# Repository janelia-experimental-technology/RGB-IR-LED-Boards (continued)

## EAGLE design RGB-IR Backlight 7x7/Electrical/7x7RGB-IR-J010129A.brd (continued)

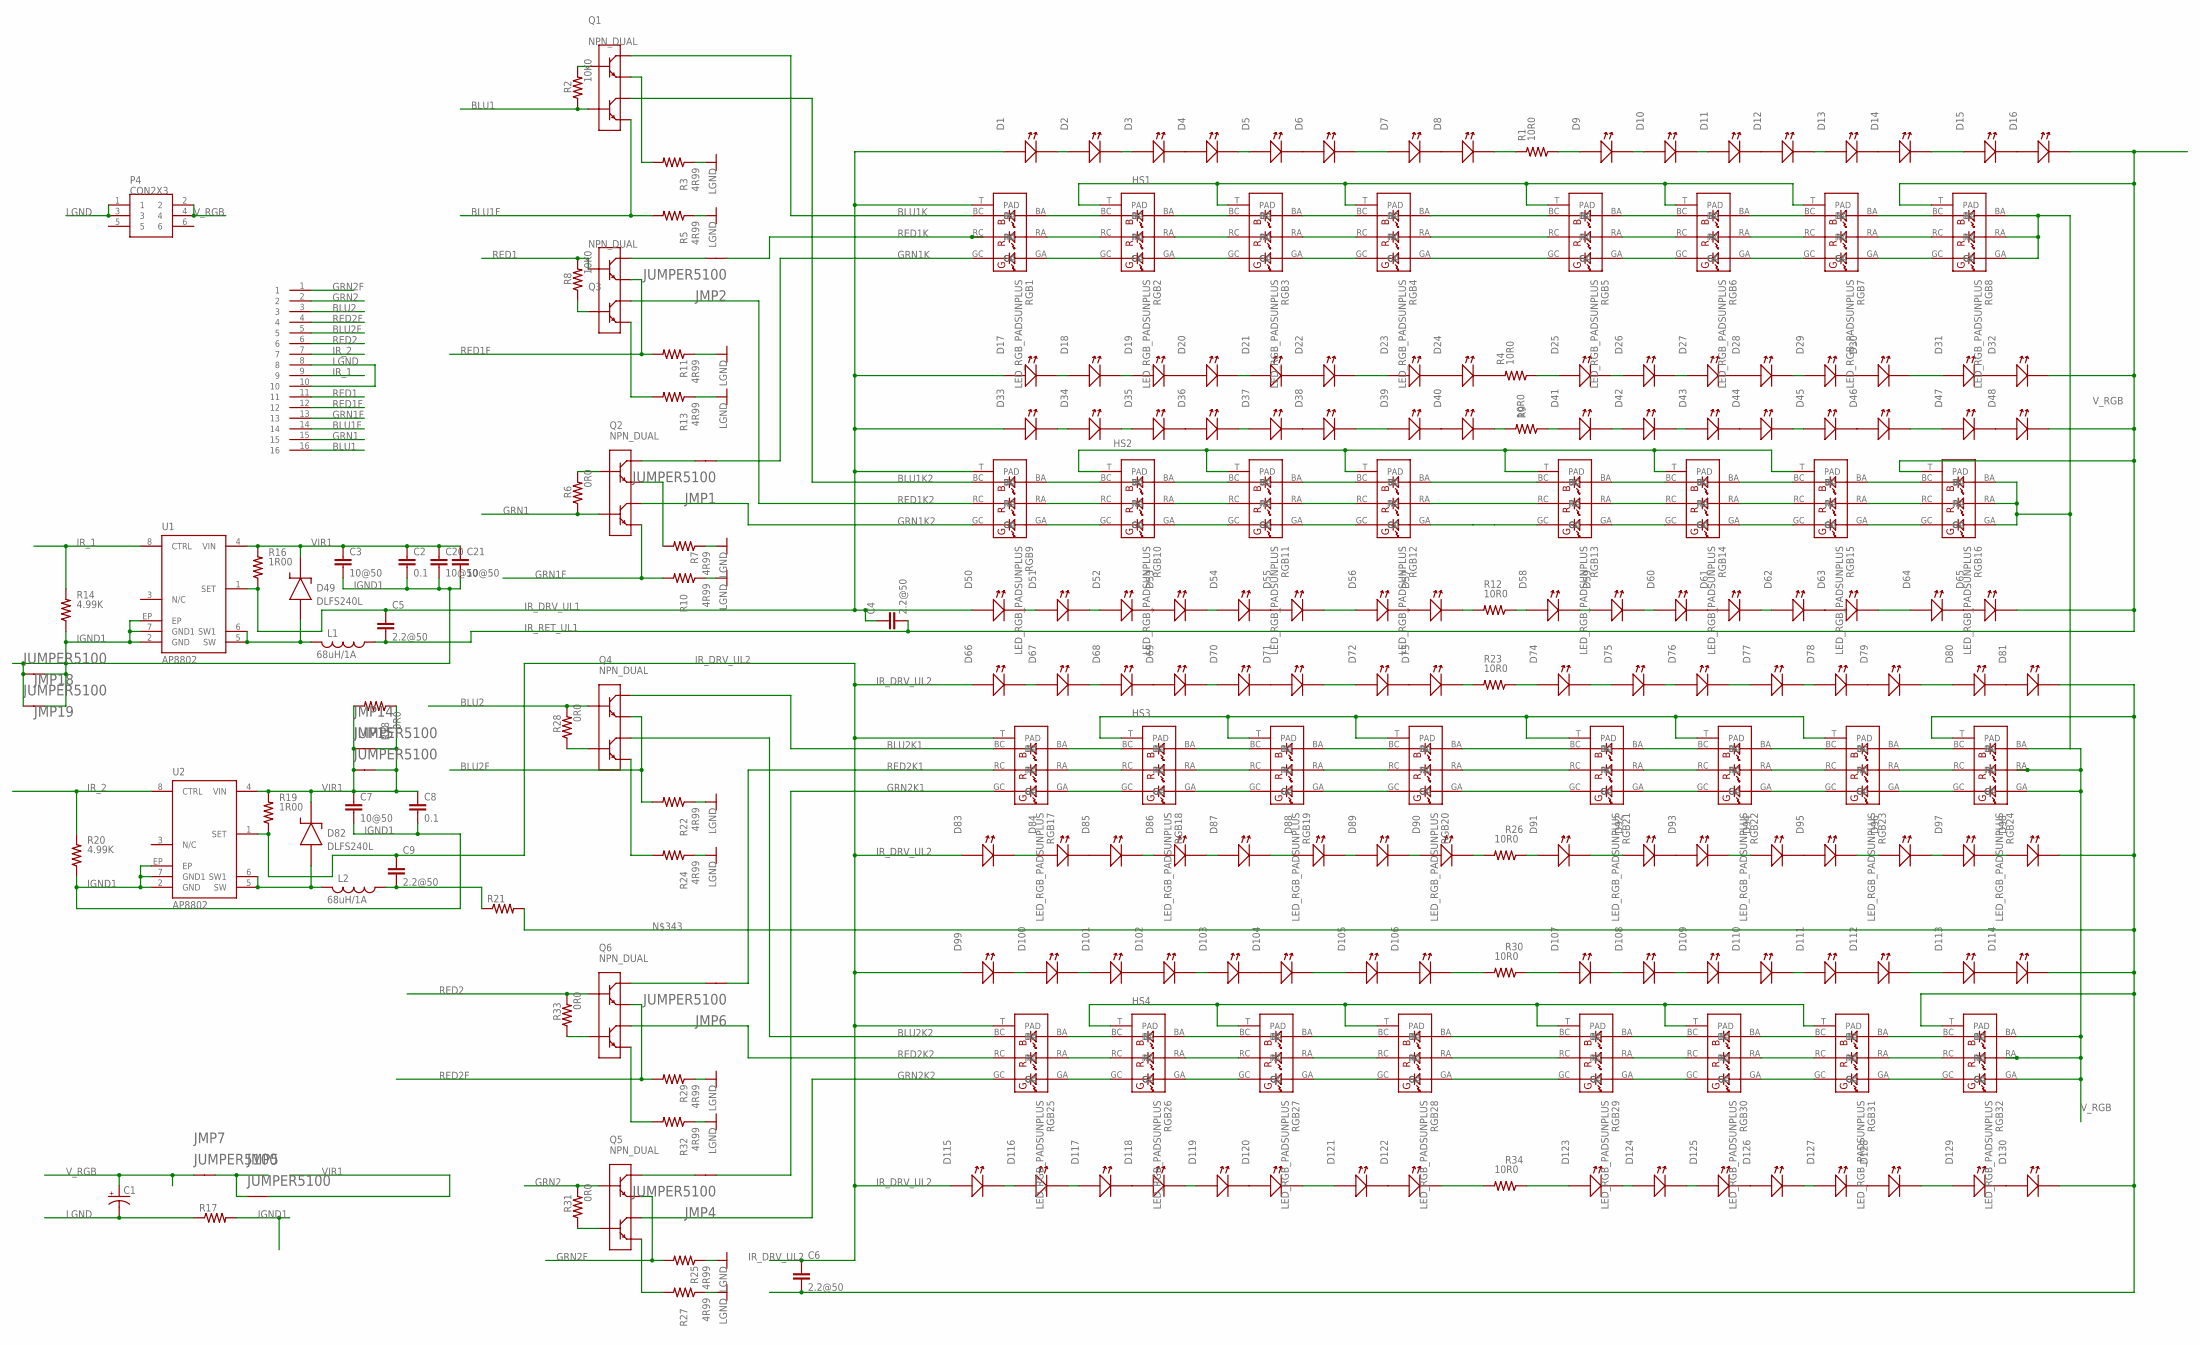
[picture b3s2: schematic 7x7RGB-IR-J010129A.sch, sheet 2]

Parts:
C1: CPOL-US153CLV-0810; 153CLV-0810
C2, C8: 0.1; 0805S
C3, C7, C20, C21: 10@50; 1210S
C4, C5, C6, C9: 2.2@50; 1206S
D1, D2, D3, D4, D5, D6, D7, D8, D9, D10, D11, D12, D13, D14, D15, D16, D17, D18, D19, D20, D21, D22, D23, D24, D25, D26, D27, D28, D29, D30, D31, D32, D33, D34, D35, D36, D37, D38, D39, D40, D41, D42, D43, D44, D45, D46, D47, D48, D50, D51, D52, D53, D54, D55, D56, D57, D58, D59, D60, D61, D62, D63, D64, D65, D66, D67, D68, D69, D70, D71, D72, D73, D74, D75, D76, D77, D78, D79, D80, D81, D83, D84, D85, D86, D87, D88, D89, D90, D91, D92, D93, D94, D95, D96, D97, D98, D99, D100, D101, D102, D103, D104, D105, D106, D107, D108, D109, D110, D111, D112, D113, D114, D115, D116, D117, D118, D119, D120, D121, D122, D123, D124, D125, D126, D127, D128, D129, D130: LEDLED_SFH4050; LED_SFH4050
D49, D82: DLFS240L; PWRDI-123
JMP1, JMP2, JMP4, JMP5, JMP6, JMP7, JMP14, JMP15, JMP18, JMP19: JUMPER5100; 5100
L1, L2: 68uH/1A; SRU8043
P1: CON162X8SM-SMALL; HEADER2X8_SM_SMALL
P4: CON2X3; 2X3_SHROUDED_SMT
Q1, Q2, Q3, Q4, Q5, Q6: NPN_DUAL; LFPAK56D
R1, R4, R9, R12, R23, R26, R30, R34: 10R0; 1206S
R2, R8: 10K0; 1206S
R3, R5, R7, R10, R11, R13, R22, R24, R25, R27, R29, R32: 4R99; R2512
R6, R28, R31, R33: 0R0; 1206S
R14, R20: 4.99K; 0805S
R16, R19: 1R00; 1206S
R17, R21: RESISTOR_SM1206S; 1206S
R18: 0R0; R1206
RGB1, RGB2, RGB3, RGB4, RGB5, RGB6, RGB7, RGB8, RGB9, RGB10, RGB11, RGB12, RGB13, RGB14, RGB15, RGB16, RGB17, RGB18, RGB19, RGB20, RGB21, RGB22, RGB23, RGB24, RGB25, RGB26, RGB27, RGB28, RGB29, RGB30, RGB31, RGB32: LED_RGB_PADSUNPLUS; SUNPLUS_RGB
U1, U2: AP8802; SOIC8-EP

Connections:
BLU1: P1.16, Q1.4 (B2), R2.1
BLU1F: P1.14, Q1.3 (E2), R5.2
BLU1K: Q1.7 (C1), Q1.8 (C1), Q1.78 (C1), RGB1.BC
BLU1K2: Q1.5 (C2), Q1.6 (C2), Q1.56 (C2), RGB9.BC
BLU2: P1.3, Q4.2 (B1), R28.2
BLU2F: P1.5, Q4.1 (E1), R22.2
BLU2K1: Q4.7 (C1), Q4.8 (C1), Q4.78 (C1), RGB17.BC
BLU2K2: Q4.5 (C2), Q4.6 (C2), Q4.56 (C2), RGB25.BC
G1: Q5.3 (E2), R27.2
G4A1: Q5.4 (B2), R31.1
GRN1: P1.15, Q2.4 (B2), R6.1
GRN1F: P1.13, Q2.3 (E2), R10.2
GRN1K: JMP1.1, RGB1.GC
GRN1K2: Q2.5 (C2), Q2.6 (C2), Q2.56 (C2), RGB9.GC
GRN2: P1.2, Q5.2 (B1), R31.2
GRN2F: P1.1, Q5.1 (E1), R25.2
GRN2K1: JMP4.1, RGB17.GC
GRN2K2: Q5.5 (C2), Q5.6 (C2), Q5.56 (C2), RGB25.GC
HS1: RGB2.T (PAD), RGB3.T (PAD), RGB4.T (PAD), RGB5.T (PAD), RGB6.T (PAD), RGB7.T (PAD)
HS2: RGB10.T (PAD), RGB11.T (PAD), RGB12.T (PAD), RGB13.T (PAD), RGB14.T (PAD), RGB15.T (PAD)
HS3: RGB18.T (PAD), RGB19.T (PAD), RGB20.T (PAD), RGB21.T (PAD), RGB22.T (PAD), RGB23.T (PAD)
HS4: RGB26.T (PAD), RGB27.T (PAD), RGB28.T (PAD), RGB29.T (PAD), RGB30.T (PAD), RGB31.T (PAD)
IGND1: C2.2, C3.2, C7.2, C8.2, C20.2, C21.2, JMP18.1, JMP18.2, JMP19.1, JMP19.2, R14.1, R17.2, R20.1, U1.2 (GND), U1.7 (GND1), U1.EP, U2.2 (GND), U2.7 (GND1), U2.EP
IR_1: P1.9, R14.2, U1.8 (CTRL)
IR_2: P1.7, R20.2, U2.8 (CTRL)
IR_DRV_UL1: C4.1, C5.1, D1.A, D17.A, D33.A, D50.A, R16.1, RGB1.T (PAD), RGB9.T (PAD), U1.1 (SET)
IR_DRV_UL2: C6.1, C9.1, D66.A, D83.A, D99.A, D115.A, R19.1, RGB17.T (PAD), RGB25.T (PAD), U2.1 (SET)
IR_RET_UL1: C4.2, C5.2, D16.C (K), D32.C (K), D48.C (K), D65.C (K), L1.1, RGB8.T (PAD), RGB16.T (PAD)
LGND: C1.-, P1.8, P1.10, P4.1, P4.3, R3.1, R5.1, R7.1, R10.1, R11.1, R13.1, R17.1, R22.1, R24.1, R25.1, R27.1, R29.1, R32.1; also elsewhere on the board
unnamed: RGB15.GA, RGB16.GC
unnamed: RGB14.GA, RGB15.GC
unnamed: RGB13.GA, RGB14.GC
unnamed: RGB12.GA, RGB13.GC
unnamed: RGB11.GA, RGB12.GC
unnamed: RGB10.GA, RGB11.GC
unnamed: RGB9.GA, RGB10.GC
unnamed: RGB15.RA, RGB16.RC
unnamed: RGB14.RA, RGB15.RC
unnamed: RGB13.RA, RGB14.RC
unnamed: RGB12.RA, RGB13.RC
unnamed: RGB11.RA, RGB12.RC
unnamed: RGB10.RA, RGB11.RC
unnamed: RGB9.RA, RGB10.RC
unnamed: RGB9.BA, RGB10.BC
unnamed: RGB10.BA, RGB11.BC
unnamed: RGB11.BA, RGB12.BC
unnamed: RGB12.BA, RGB13.BC
unnamed: RGB13.BA, RGB14.BC
unnamed: RGB14.BA, RGB15.BC
unnamed: RGB15.BA, RGB16.BC
unnamed: D51.C (K), D52.A
unnamed: D52.C (K), D53.A
unnamed: D54.C (K), D55.A
unnamed: D56.C (K), D57.A
unnamed: D50.C (K), D51.A
unnamed: D53.C (K), D54.A
unnamed: D55.C (K), D56.A
unnamed: D59.C (K), D60.A
unnamed: D60.C (K), D61.A
unnamed: D62.C (K), D63.A
unnamed: D64.C (K), D65.A
unnamed: D58.C (K), D59.A
unnamed: D61.C (K), D62.A
unnamed: D63.C (K), D64.A
unnamed: D34.C (K), D35.A
unnamed: D35.C (K), D36.A
unnamed: D37.C (K), D38.A
unnamed: D39.C (K), D40.A
unnamed: D33.C (K), D34.A
unnamed: D36.C (K), D37.A
unnamed: D38.C (K), D39.A
unnamed: D42.C (K), D43.A
unnamed: D43.C (K), D44.A
unnamed: D45.C (K), D46.A
unnamed: D47.C (K), D48.A
unnamed: D41.C (K), D42.A
unnamed: D44.C (K), D45.A
unnamed: D46.C (K), D47.A
unnamed: RGB23.GA, RGB24.GC
unnamed: RGB22.GA, RGB23.GC
unnamed: RGB21.GA, RGB22.GC
unnamed: RGB20.GA, RGB21.GC
unnamed: RGB19.GA, RGB20.GC
unnamed: RGB18.GA, RGB19.GC
unnamed: RGB17.GA, RGB18.GC
unnamed: RGB23.RA, RGB24.RC
unnamed: RGB22.RA, RGB23.RC
unnamed: RGB21.RA, RGB22.RC
unnamed: RGB20.RA, RGB21.RC
unnamed: RGB19.RA, RGB20.RC
unnamed: RGB18.RA, RGB19.RC
unnamed: RGB17.RA, RGB18.RC
unnamed: RGB17.BA, RGB18.BC
unnamed: RGB18.BA, RGB19.BC
unnamed: RGB19.BA, RGB20.BC
unnamed: RGB20.BA, RGB21.BC
unnamed: RGB21.BA, RGB22.BC
unnamed: RGB22.BA, RGB23.BC
unnamed: RGB23.BA, RGB24.BC
unnamed: D67.C (K), D68.A
unnamed: D68.C (K), D69.A
unnamed: D70.C (K), D71.A
unnamed: D72.C (K), D73.A
unnamed: D66.C (K), D67.A
unnamed: D69.C (K), D70.A
unnamed: D71.C (K), D72.A
unnamed: D75.C (K), D76.A
unnamed: D76.C (K), D77.A
unnamed: D78.C (K), D79.A
unnamed: D80.C (K), D81.A
unnamed: D74.C (K), D75.A
unnamed: D77.C (K), D78.A
unnamed: D79.C (K), D80.A
unnamed: D84.C (K), D85.A
unnamed: D85.C (K), D86.A
unnamed: D87.C (K), D88.A
unnamed: D89.C (K), D90.A
unnamed: D83.C (K), D84.A
unnamed: D86.C (K), D87.A
unnamed: D88.C (K), D89.A
unnamed: D92.C (K), D93.A
unnamed: D94.C (K), D95.A
unnamed: D96.C (K), D97.A
unnamed: D91.C (K), D92.A
unnamed: D93.C (K), D94.A
unnamed: D95.C (K), D96.A
unnamed: RGB7.GA, RGB8.GC
unnamed: RGB6.GA, RGB7.GC
unnamed: RGB5.GA, RGB6.GC
unnamed: RGB4.GA, RGB5.GC
unnamed: RGB3.GA, RGB4.GC
unnamed: RGB2.GA, RGB3.GC
unnamed: RGB1.GA, RGB2.GC
unnamed: RGB7.RA, RGB8.RC
unnamed: RGB6.RA, RGB7.RC
unnamed: RGB5.RA, RGB6.RC
unnamed: RGB4.RA, RGB5.RC
unnamed: RGB3.RA, RGB4.RC
unnamed: RGB2.RA, RGB3.RC
unnamed: RGB1.RA, RGB2.RC
unnamed: RGB1.BA, RGB2.BC
unnamed: RGB2.BA, RGB3.BC
unnamed: RGB3.BA, RGB4.BC
unnamed: RGB4.BA, RGB5.BC
unnamed: RGB5.BA, RGB6.BC
unnamed: RGB6.BA, RGB7.BC
unnamed: RGB7.BA, RGB8.BC
unnamed: D2.C (K), D3.A
unnamed: D3.C (K), D4.A
unnamed: D5.C (K), D6.A
unnamed: D7.C (K), D8.A
unnamed: D1.C (K), D2.A
unnamed: D4.C (K), D5.A
unnamed: D6.C (K), D7.A
unnamed: D10.C (K), D11.A
unnamed: D11.C (K), D12.A
unnamed: D13.C (K), D14.A
unnamed: D15.C (K), D16.A
unnamed: D9.C (K), D10.A
unnamed: D12.C (K), D13.A
unnamed: D14.C (K), D15.A
unnamed: D18.C (K), D19.A
unnamed: D19.C (K), D20.A
unnamed: D21.C (K), D22.A
unnamed: D23.C (K), D24.A
unnamed: D17.C (K), D18.A
unnamed: D20.C (K), D21.A
unnamed: D22.C (K), D23.A
unnamed: D26.C (K), D27.A
unnamed: D27.C (K), D28.A
unnamed: D29.C (K), D30.A
unnamed: D31.C (K), D32.A
unnamed: D25.C (K), D26.A
unnamed: D28.C (K), D29.A
unnamed: D30.C (K), D31.A
unnamed: Q1.1 (E1), R3.2
unnamed: RGB31.GA, RGB32.GC
unnamed: RGB30.GA, RGB31.GC
unnamed: RGB29.GA, RGB30.GC
unnamed: RGB28.GA, RGB29.GC
unnamed: RGB27.GA, RGB28.GC
unnamed: RGB26.GA, RGB27.GC
unnamed: RGB25.GA, RGB26.GC
unnamed: RGB31.RA, RGB32.RC
unnamed: RGB30.RA, RGB31.RC
unnamed: RGB29.RA, RGB30.RC
unnamed: RGB28.RA, RGB29.RC
unnamed: RGB27.RA, RGB28.RC
unnamed: RGB26.RA, RGB27.RC
unnamed: RGB25.RA, RGB26.RC
unnamed: RGB25.BA, RGB26.BC
unnamed: RGB26.BA, RGB27.BC
unnamed: RGB27.BA, RGB28.BC
unnamed: RGB28.BA, RGB29.BC
unnamed: RGB29.BA, RGB30.BC
unnamed: RGB30.BA, RGB31.BC
unnamed: RGB31.BA, RGB32.BC
unnamed: D100.C (K), D101.A
unnamed: D101.C (K), D102.A
unnamed: D103.C (K), D104.A
unnamed: D105.C (K), D106.A
unnamed: D99.C (K), D100.A
unnamed: D102.C (K), D103.A
unnamed: D104.C (K), D105.A
unnamed: D108.C (K), D109.A
unnamed: D109.C (K), D110.A
unnamed: D111.C (K), D112.A
unnamed: D113.C (K), D114.A
unnamed: D107.C (K), D108.A
unnamed: D110.C (K), D111.A
unnamed: D112.C (K), D113.A
unnamed: D116.C (K), D117.A
unnamed: D117.C (K), D118.A
unnamed: D119.C (K), D120.A
unnamed: D121.C (K), D122.A
unnamed: D115.C (K), D116.A
unnamed: D118.C (K), D119.A
unnamed: D120.C (K), D121.A
unnamed: D124.C (K), D125.A
unnamed: D125.C (K), D126.A
unnamed: D127.C (K), D128.A
unnamed: D129.C (K), D130.A
unnamed: D123.C (K), D124.A
unnamed: D126.C (K), D127.A
unnamed: D128.C (K), D129.A
unnamed: JMP2.2, Q3.7 (C1), Q3.8 (C1), Q3.78 (C1)
unnamed: JMP1.2, Q2.7 (C1), Q2.8 (C1), Q2.78 (C1)
unnamed: Q1.2 (B1), R2.2
unnamed: D97.C (K), D98.A
unnamed: JMP6.2, Q6.7 (C1), Q6.8 (C1), Q6.78 (C1)
unnamed: JMP4.2, Q5.7 (C1), Q5.8 (C1), Q5.78 (C1)
unnamed: D49.A, L1.2, U1.5 (SW), U1.6 (SW1)
unnamed: D82.A, L2.2, U2.5 (SW), U2.6 (SW1)
unnamed: C6.2, D81.C (K), D98.C (K), D114.C (K), D130.C (K), R21.2, RGB24.T (PAD), RGB32.T (PAD)
unnamed: C9.2, L2.1, R21.1
unnamed: JMP5.1, JMP7.2
unnamed: Q6.4 (B2), R33.1
unnamed: Q4.4 (B2), R28.1
unnamed: Q4.3 (E2), R24.2
unnamed: Q3.3 (E2), R13.2
unnamed: Q3.4 (B2), R8.1
unnamed: Q2.1 (E1), R7.2
unnamed: Q2.2 (B1), R6.2
unnamed: D9.A, R1.1
unnamed: D8.C (K), R1.2
unnamed: D24.C (K), R4.2
unnamed: D25.A, R4.1
unnamed: D41.A, R9.1
unnamed: D40.C (K), R9.2
unnamed: D58.A, R12.1
unnamed: D57.C (K), R12.2
unnamed: D73.C (K), R23.2
unnamed: D74.A, R23.1
unnamed: D91.A, R26.1
unnamed: D90.C (K), R26.2
unnamed: D107.A, R30.1
unnamed: D106.C (K), R30.2
unnamed: D123.A, R34.1
unnamed: D122.C (K), R34.2
R1: Q6.3 (E2), R32.2
RED1: P1.11, Q3.2 (B1), R8.2
RED1F: P1.12, Q3.1 (E1), R11.2
RED1K: JMP2.1, RGB1.RC
RED1K2: Q3.5 (C2), Q3.6 (C2), Q3.56 (C2), RGB9.RC
RED2: P1.6, Q6.2 (B1), R33.2
RED2F: P1.4, Q6.1 (E1), R29.2
RED2K1: JMP6.1, RGB17.RC
RED2K2: Q6.5 (C2), Q6.6 (C2), Q6.56 (C2), RGB25.RC
VIR1: C2.1, C3.1, C7.1, C8.1, C20.1, C21.1, D49.K, D82.K, JMP5.2, JMP14.1, JMP14.2, JMP15.1, JMP15.2, R16.2, R18.1, R18.2, R19.2, U1.4 (VIN), U2.4 (VIN)
V_RGB: C1.+, JMP7.1, P4.2, P4.4, RGB8.BA, RGB8.GA, RGB8.RA, RGB16.BA, RGB16.GA, RGB16.RA, RGB24.BA, RGB24.GA, RGB24.RA, RGB32.BA, RGB32.GA, RGB32.RA; also elsewhere on the board

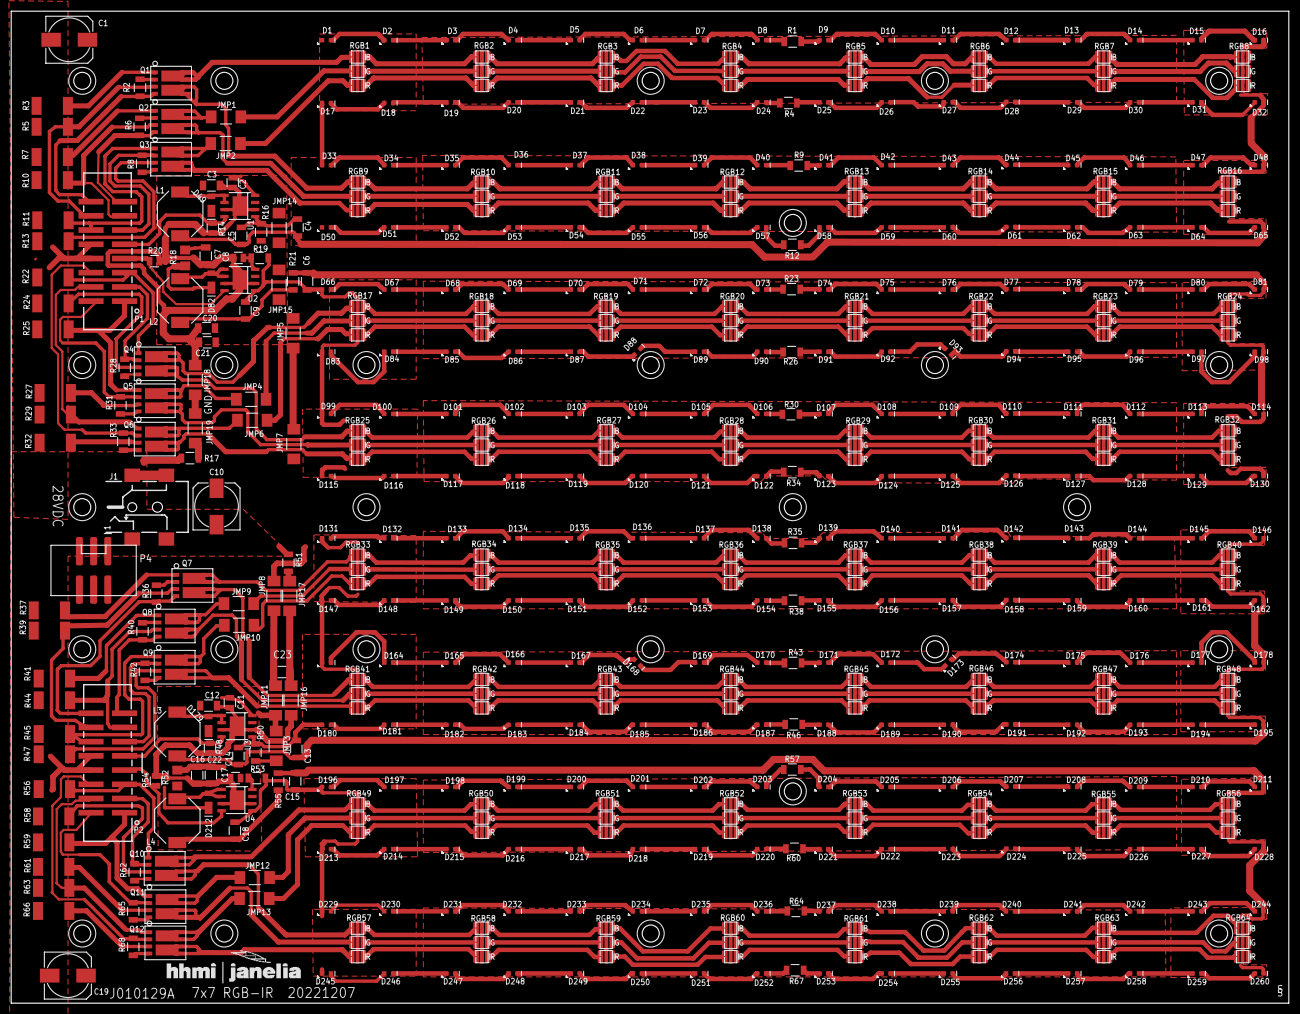
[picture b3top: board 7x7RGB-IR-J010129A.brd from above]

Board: 2 copper layers, 228.3 x 177.3 mm, 485 parts (0 on the bottom side), 537 nets.

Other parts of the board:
S1, S2, S3, S4, S5, S6, S7, S8, S9, S10, S11, S12, S13, S14, S15, S16, S17, S18, S19, S20, S21, S22, S23, S24, S25, S26, S27, S28: SCREW; 4-40SOCKET

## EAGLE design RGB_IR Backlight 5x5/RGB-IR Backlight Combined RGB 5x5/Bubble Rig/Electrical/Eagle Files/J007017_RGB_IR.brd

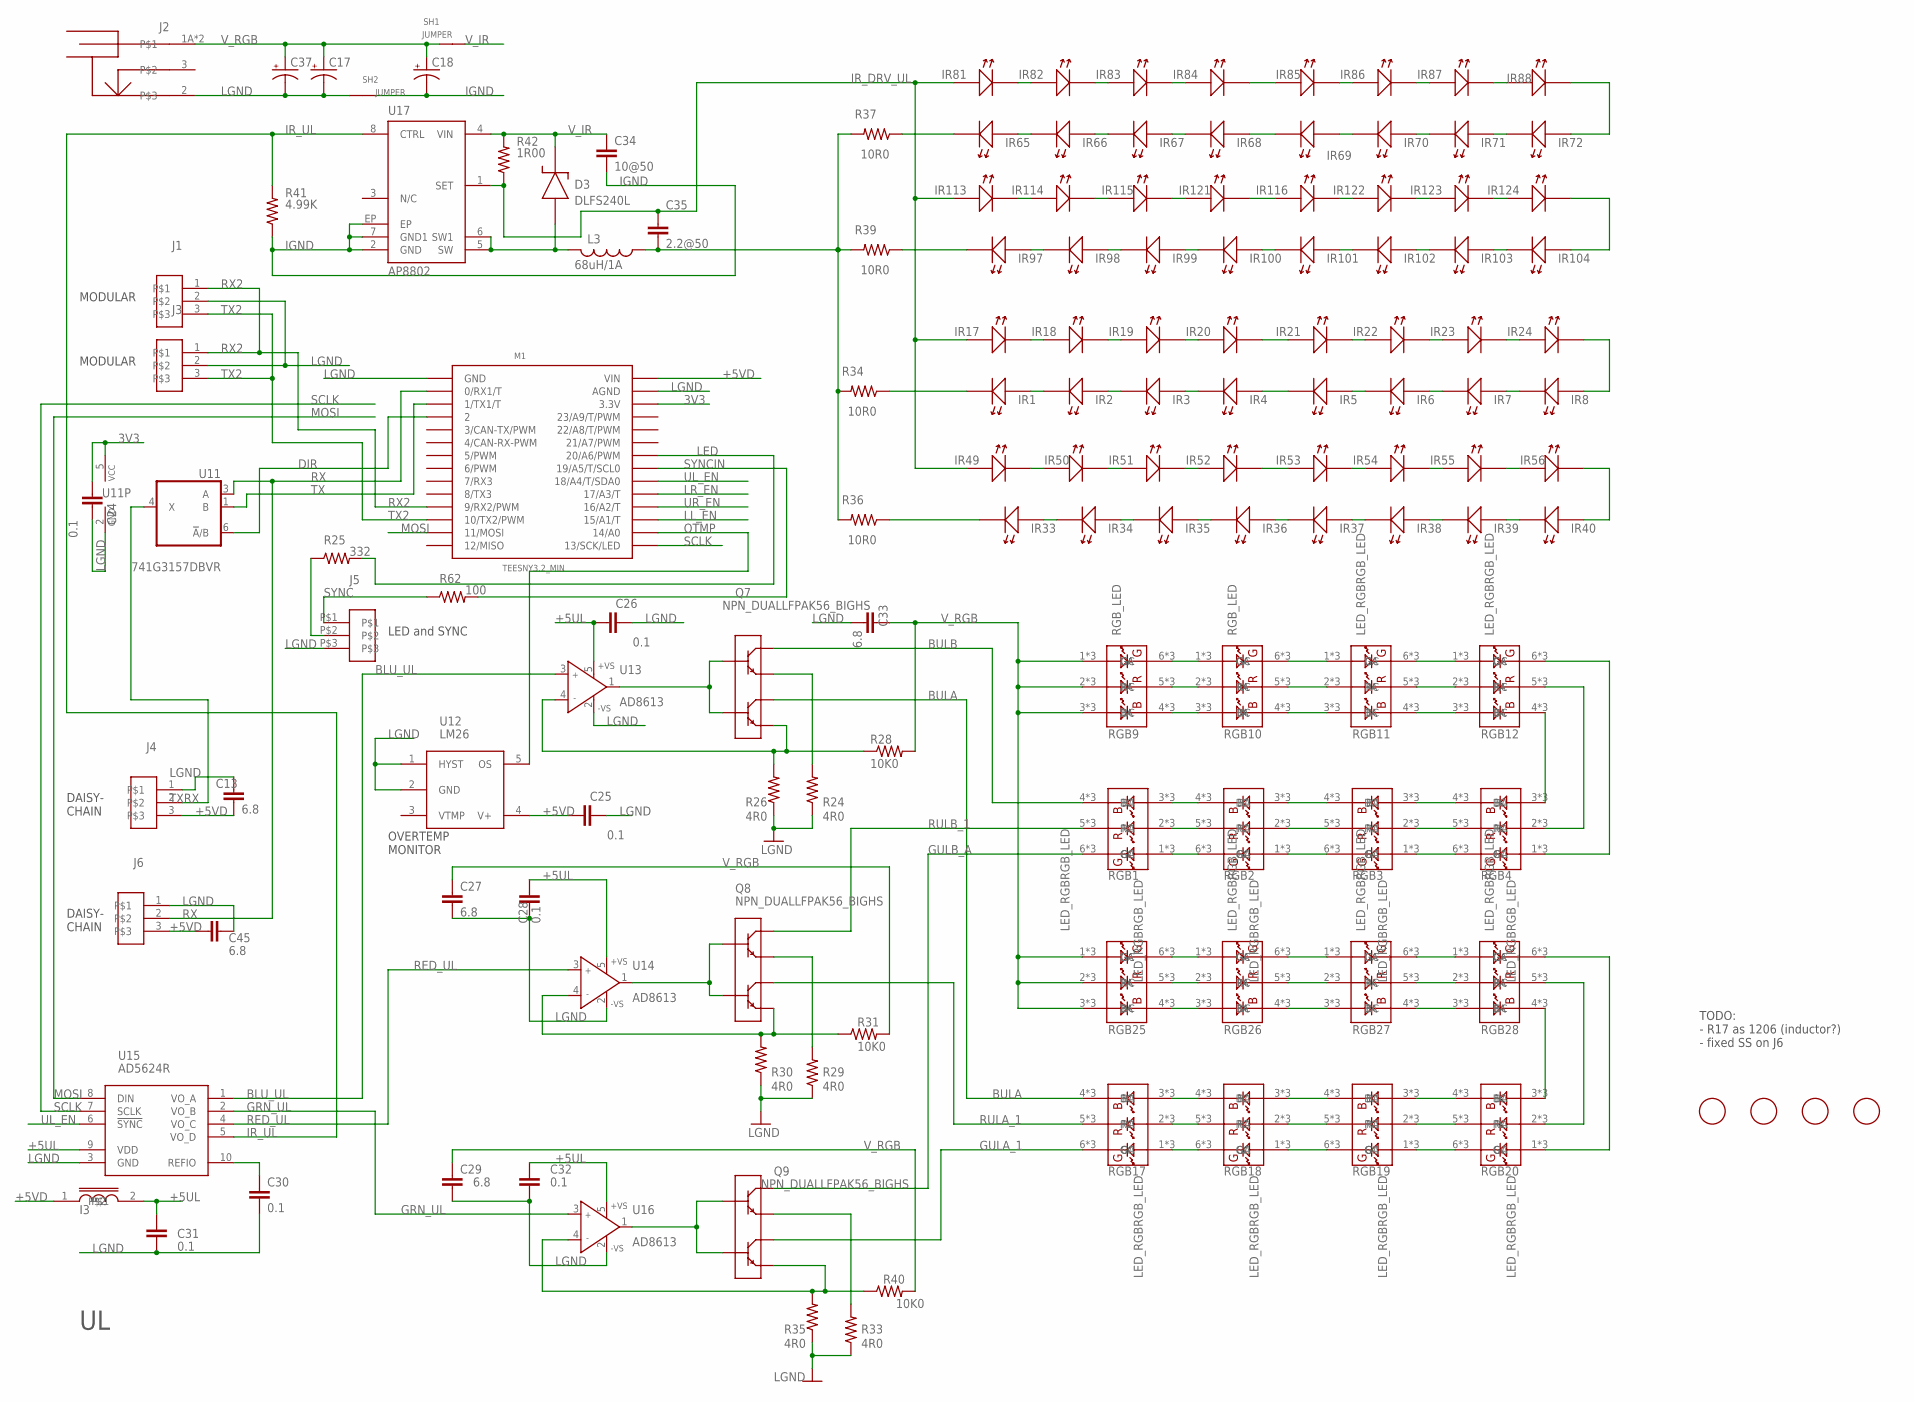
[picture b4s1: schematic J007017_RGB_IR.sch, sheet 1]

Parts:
$$U$1, $$U$2, $$U$3: FIDUCIAL; FIDUCIAL_1MM
C13, C27, C29, C33, C45: 6.8; 1210S
C17, C18, C37: CPOL-US153CLV-0810; 153CLV-0810
C24, C25, C26, C28, C30, C31, C32: 0.1; 0603S
C34: 10@50; 1210S
C35: 2.2@50; 1206S
D3: DLFS240L; PWRDI-123
I3: INDUCTOR0805S; 0805S
IR1: LEDLED_SFH4050_A; LED_SFH4045_HEAT_A
IR2, IR3, IR4, IR5, IR6, IR7, IR8, IR17, IR18, IR19, IR20, IR21, IR22, IR23, IR24, IR33, IR34, IR35, IR36, IR37, IR38, IR39, IR40, IR49, IR50, IR51, IR52, IR53, IR54, IR55, IR56, IR65, IR66, IR67, IR68, IR69, IR70, IR71, IR72, IR81, IR82, IR83, IR84, IR85, IR86, IR87, IR88, IR97, IR98, IR99, IR100, IR101, IR102, IR103, IR104, IR113, IR114, IR115, IR116, IR121, IR122, IR123: LEDLED_SFH4050_HEAT; LED_SFH4050_HEAT
IR124: LEDLED_SFH4050; LED_SFH4050
J1: CON3AMP-3-SM-RA-X; AMP-3-SM-RA-X
J2: POWER_JACK_SHUNTPJ-002; PJ-002
J3: CON3AMP_3_SM; AMP_3_SM
J4, J6: CON3TE-3-SM-V; TE_3_SM-V
J5: CON3DF13-3-V-SM; DF13_3_V_SM
L3: 68uH/1A; SRU8043
M1: TEESNY3.2_MIN; TEENSY3.2_MIN_SM
Q7, Q8, Q9: NPN_DUALLFPAK56_BIGHS; LFPAK56_HS2
R24, R26, R29, R30, R33, R35: 4R0; 1812
R25: 332; 0805S
R28, R31, R40: 10K0; 1206S
R34, R36, R37, R39: 10R0; 1206S
R41: 4.99K; 0805S
R42: 1R00; 1206S
R62: 100; 0805S
RGB1, RGB2, RGB3, RGB4, RGB11, RGB12, RGB17, RGB18, RGB19, RGB20, RGB25, RGB26, RGB27, RGB28: LED_RGBRGB_LED; OVSPRGB_HS_FIXED
RGB9, RGB10: RGB_LED; OVSPRGB_HS_FIXED
SH1, SH2: JUMPER
U11: 741G3157DBVR; DBV_R-PDSO-G6
U12: LM26; SOT23-5
U13, U14, U16: AD8613; SOT23-5
U15: AD5624R; MSOP10
U17: AP8802; SOIC8-EP
U$2: FIDUCIAL; FIDUCIAL_1MM

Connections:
3V3: C24.1, M1.26 (3.3V), U11.5 (VCC)
+5UL: C26.1, C28.1, C31.1, C32.1, I3.2, U13.5 (+VS), U14.5 (+VS), U15.9 (VDD), U16.5 (+VS)
+5VD: C13.2, C25.1, C45.1, I3.1, J4.3, J6.3, M1.28 (VIN), U12.4 (V+); also elsewhere on the board
BLU_UL: U13.3 (IN+), U15.1 (VO_A)
BULA: Q7.5 (C2), Q7.5A (C2), Q7.5A1 (C2), Q7.5B (C2), Q7.5C (C2), Q7.5C1 (C2), Q7.5C2 (C2), Q7.6 (C2), Q7.56 (C2), Q7.56A (C2), Q7.56B (C2), RGB17.4 (BC), RGB17.4A (BC), RGB17.4B (BC)
BULB: Q7.7 (C1), Q7.8 (C1), Q7.8A (C1), Q7.8B (C1), Q7.8C (C1), Q7.8C1 (C1), Q7.8C2 (C1), Q7.8C3 (C1), Q7.78 (C1), Q7.78A (C1), Q7.78B (C1), RGB1.4 (BC), RGB1.4A (BC), RGB1.4B (BC)
DIR: M1.4 (2), U11.6 (!A!/B)
GRN_UL: U15.2 (VO_B), U16.3 (IN+)
GULA_1: Q9.5 (C2), Q9.5A (C2), Q9.5A1 (C2), Q9.5B (C2), Q9.5C (C2), Q9.5C1 (C2), Q9.5C2 (C2), Q9.6 (C2), Q9.56 (C2), Q9.56A (C2), Q9.56B (C2), RGB17.6 (GC), RGB17.6A (GC), RGB17.6B (GC)
GULB_A: Q9.7 (C1), Q9.8 (C1), Q9.8A (C1), Q9.8B (C1), Q9.8C (C1), Q9.8C1 (C1), Q9.8C2 (C1), Q9.8C3 (C1), Q9.78 (C1), Q9.78A (C1), Q9.78B (C1), RGB1.6 (GC), RGB1.6A (GC), RGB1.6B (GC)
IGND: C18.-, C34.2, R41.1, SH2.2, U17.2 (GND), U17.7 (GND1), U17.EP; also elsewhere on the board
IR_DRV_UL: C35.1, IR17.A, IR17.A1 (A), IR49.A, IR49.A1 (A), IR81.A, IR81.A1 (A), IR113.A, IR113.A1 (A), R42.1, U17.1 (SET)
IR_RET_UL: C35.2, L3.1, R34.2, R36.2, R37.2, R39.2
IR_UL: R41.2, U15.5 (VO_D), U17.8 (CTRL)
LED: M1.22 (20/A6/PWM), R25.2
LGND: C13.1, C17.-, C24.2, C25.2, C26.2, C27.2, C28.2, C29.2, C30.2, C31.2, C32.2, C33.2, C37.-, C45.2, J1.2, J2.2, J3.2, J4.1, J5.P$3, J6.1, M1.1 (GND), M1.27 (AGND), R24.1, R26.1, R29.1, R30.1, R33.1, R35.1, SH2.1, U11.2 (GND), U12.1 (HYST), U12.2 (GND), U13.2 (-VS), U14.2 (-VS), U15.3 (GND), U16.2 (-VS); also elsewhere on the board
LL_EN: M1.17 (15/A1/T); also elsewhere on the board
LR_EN: M1.19 (17/A3/T); also elsewhere on the board
MOSI: M1.13 (11/MOSI), U15.8 (DIN); also elsewhere on the board
unnamed: IR7.A, IR7.A1 (A), IR8.C (K), IR8.C1 (K)
unnamed: IR6.A, IR6.A1 (A), IR7.C (K), IR7.C1 (K)
unnamed: IR71.A, IR71.A1 (A), IR72.C (K), IR72.C1 (K)
unnamed: IR70.A, IR70.A1 (A), IR71.C (K), IR71.C1 (K)
unnamed: IR69.A, IR69.A1 (A), IR70.C (K), IR70.C1 (K)
unnamed: IR67.A, IR67.A1 (A), IR68.C (K), IR68.C1 (K)
unnamed: IR66.A, IR66.A1 (A), IR67.C (K), IR67.C1 (K)
unnamed: IR65.A, IR65.A1 (A), IR66.C (K), IR66.C1 (K)
unnamed: IR5.A, IR5.A1 (A), IR6.C (K), IR6.C1 (K)
unnamed: IR3.A, IR3.A1 (A), IR4.C (K), IR4.C1 (K)
unnamed: IR2.A, IR2.A1 (A), IR3.C (K), IR3.C1 (K)
unnamed: IR1.A, IR1.A1 (A), IR2.C (K), IR2.C1 (K)
unnamed: IR17.C (K), IR17.C1 (K), IR18.A, IR18.A1 (A)
unnamed: IR81.C (K), IR81.C1 (K), IR82.A, IR82.A1 (A)
unnamed: IR18.C (K), IR18.C1 (K), IR19.A, IR19.A1 (A)
unnamed: IR82.C (K), IR82.C1 (K), IR83.A, IR83.A1 (A)
unnamed: IR83.C (K), IR83.C1 (K), IR84.A, IR84.A1 (A)
unnamed: IR68.A, IR68.A1 (A), IR69.C (K), IR69.C1 (K)
unnamed: IR103.A, IR103.A1 (A), IR104.C (K), IR104.C1 (K)
unnamed: IR102.A, IR102.A1 (A), IR103.C (K), IR103.C1 (K)
unnamed: IR101.A, IR101.A1 (A), IR102.C (K), IR102.C1 (K)
unnamed: IR100.A, IR100.A1 (A), IR101.C (K), IR101.C1 (K)
unnamed: IR99.A, IR99.A1 (A), IR100.C (K), IR100.C1 (K)
unnamed: IR19.C (K), IR19.C1 (K), IR20.A, IR20.A1 (A)
unnamed: IR4.A, IR4.A1 (A), IR5.C (K), IR5.C1 (K)
unnamed: IR39.A, IR39.A1 (A), IR40.C (K), IR40.C1 (K)
unnamed: IR38.A, IR38.A1 (A), IR39.C (K), IR39.C1 (K)
unnamed: IR37.A, IR37.A1 (A), IR38.C (K), IR38.C1 (K)
unnamed: IR98.A, IR98.A1 (A), IR99.C (K), IR99.C1 (K)
unnamed: IR36.A, IR36.A1 (A), IR37.C (K), IR37.C1 (K)
unnamed: IR35.A, IR35.A1 (A), IR36.C (K), IR36.C1 (K)
unnamed: IR97.A, IR97.A1 (A), IR98.C (K), IR98.C1 (K)
unnamed: IR85.C (K), IR85.C1 (K), IR86.A, IR86.A1 (A)
unnamed: IR86.C (K), IR86.C1 (K), IR87.A, IR87.A1 (A)
unnamed: IR34.A, IR34.A1 (A), IR35.C (K), IR35.C1 (K)
unnamed: IR87.C (K), IR87.C1 (K), IR88.A, IR88.A1 (A)
unnamed: IR33.A, IR33.A1 (A), IR34.C (K), IR34.C1 (K)
unnamed: IR21.C (K), IR21.C1 (K), IR22.A, IR22.A1 (A)
unnamed: IR22.C (K), IR22.C1 (K), IR23.A, IR23.A1 (A)
unnamed: IR23.C (K), IR23.C1 (K), IR24.A, IR24.A1 (A)
unnamed: IR49.C (K), IR49.C1 (K), IR50.A, IR50.A1 (A)
unnamed: IR50.C (K), IR50.C1 (K), IR51.A, IR51.A1 (A)
unnamed: IR51.C (K), IR51.C1 (K), IR52.A, IR52.A1 (A)
unnamed: IR53.C (K), IR53.C1 (K), IR54.A, IR54.A1 (A)
unnamed: IR54.C (K), IR54.C1 (K), IR55.A, IR55.A1 (A)
unnamed: IR55.C (K), IR55.C1 (K), IR56.A, IR56.A1 (A)
unnamed: IR113.C (K), IR113.C1 (K), IR114.A, IR114.A1 (A)
unnamed: IR20.C (K), IR20.C1 (K), IR21.A, IR21.A1 (A)
unnamed: IR114.C (K), IR114.C1 (K), IR115.A, IR115.A1 (A)
unnamed: IR8.A, IR8.A1 (A), IR24.C (K), IR24.C1 (K)
unnamed: IR52.C (K), IR52.C1 (K), IR53.A, IR53.A1 (A)
unnamed: IR115.C (K), IR115.C1 (K), IR121.A, IR121.A1 (A)
unnamed: IR1.C (K), R34.1
unnamed: IR40.A, IR40.A1 (A), IR56.C (K), IR56.C1 (K)
unnamed: IR33.C (K), IR33.C1 (K), R36.1
unnamed: RGB9.6 (GC), RGB9.6A (GC), RGB9.6B (GC), RGB10.1 (GA), RGB10.1A (GA), RGB10.1B (GA)
unnamed: RGB9.5 (RC), RGB9.5A (RC), RGB9.5B (RC), RGB10.2 (RA), RGB10.2A (RA), RGB10.2B (RA)
unnamed: IR65.C (K), IR65.C1 (K), R37.1
unnamed: RGB9.4 (BC), RGB9.4A (BC), RGB9.4B (BC), RGB10.3 (BA), RGB10.3A (BA), RGB10.3B (BA)
unnamed: IR116.C (K), IR116.C1 (K), IR122.A, IR122.A1 (A)
unnamed: RGB10.6 (GC), RGB10.6A (GC), RGB10.6B (GC), RGB11.1 (GA), RGB11.1A (GA), RGB11.1B (GA)
unnamed: IR122.C (K), IR122.C1 (K), IR123.A, IR123.A1 (A)
unnamed: IR123.C (K), IR123.C1 (K), IR124.A
unnamed: Q8.3 (E2), R30.2, R31.1, U14.4 (IN-)
unnamed: D3.A, L3.2, U17.5 (SW), U17.6 (SW1)
unnamed: IR84.C (K), IR84.C1 (K), IR85.A, IR85.A1 (A)
unnamed: RGB10.5 (RC), RGB10.5A (RC), RGB10.5B (RC), RGB11.2 (RA), RGB11.2A (RA), RGB11.2B (RA)
unnamed: IR72.A, IR72.A1 (A), IR88.C (K), IR88.C1 (K)
unnamed: C30.1, U15.10 (REFIO)
unnamed: IR116.A, IR116.A1 (A), IR121.C (K), IR121.C1 (K)
unnamed: RGB10.4 (BC), RGB10.4A (BC), RGB10.4B (BC), RGB11.3 (BA), RGB11.3A (BA), RGB11.3B (BA)
unnamed: RGB11.6 (GC), RGB11.6A (GC), RGB11.6B (GC), RGB12.1 (GA), RGB12.1A (GA), RGB12.1B (GA)
unnamed: IR104.A, IR104.A1 (A), IR124.C (K)
unnamed: RGB11.5 (RC), RGB11.5A (RC), RGB11.5B (RC), RGB12.2 (RA), RGB12.2A (RA), RGB12.2B (RA)
unnamed: IR97.C (K), IR97.C1 (K), R39.1
unnamed: Q9.3 (E2), R35.2, R40.1, U16.4 (IN-)
unnamed: RGB11.4 (BC), RGB11.4A (BC), RGB11.4B (BC), RGB12.3 (BA), RGB12.3A (BA), RGB12.3B (BA)
unnamed: RGB4.1 (GA), RGB4.1A (GA), RGB4.1B (GA), RGB12.6 (GC), RGB12.6A (GC), RGB12.6B (GC)
unnamed: Q8.1 (E1), R29.2
unnamed: RGB4.2 (RA), RGB4.2A (RA), RGB4.2B (RA), RGB12.5 (RC), RGB12.5A (RC), RGB12.5B (RC)
unnamed: Q8.2 (B1), Q8.4 (B2), U14.1 (OUT)
unnamed: RGB4.3 (BA), RGB4.3A (BA), RGB4.3B (BA), RGB12.4 (BC), RGB12.4A (BC), RGB12.4B (BC)
unnamed: RGB3.1 (GA), RGB3.1A (GA), RGB3.1B (GA), RGB4.6 (GC), RGB4.6A (GC), RGB4.6B (GC)
unnamed: RGB3.2 (RA), RGB3.2A (RA), RGB3.2B (RA), RGB4.5 (RC), RGB4.5A (RC), RGB4.5B (RC)
unnamed: RGB3.3 (BA), RGB3.3A (BA), RGB3.3B (BA), RGB4.4 (BC), RGB4.4A (BC), RGB4.4B (BC)
unnamed: RGB2.1 (GA), RGB2.1A (GA), RGB2.1B (GA), RGB3.6 (GC), RGB3.6A (GC), RGB3.6B (GC)
unnamed: RGB2.2 (RA), RGB2.2A (RA), RGB2.2B (RA), RGB3.5 (RC), RGB3.5A (RC), RGB3.5B (RC)
unnamed: RGB2.3 (BA), RGB2.3A (BA), RGB2.3B (BA), RGB3.4 (BC), RGB3.4A (BC), RGB3.4B (BC)
unnamed: RGB1.1 (GA), RGB1.1A (GA), RGB1.1B (GA), RGB2.6 (GC), RGB2.6A (GC), RGB2.6B (GC)
unnamed: RGB1.2 (RA), RGB1.2A (RA), RGB1.2B (RA), RGB2.5 (RC), RGB2.5A (RC), RGB2.5B (RC)
unnamed: RGB1.3 (BA), RGB1.3A (BA), RGB1.3B (BA), RGB2.4 (BC), RGB2.4A (BC), RGB2.4B (BC)
unnamed: Q9.2 (B1), Q9.4 (B2), U16.1 (OUT)
unnamed: RGB25.6 (GC), RGB25.6A (GC), RGB25.6B (GC), RGB26.1 (GA), RGB26.1A (GA), RGB26.1B (GA)
unnamed: RGB25.5 (RC), RGB25.5A (RC), RGB25.5B (RC), RGB26.2 (RA), RGB26.2A (RA), RGB26.2B (RA)
unnamed: RGB25.4 (BC), RGB25.4A (BC), RGB25.4B (BC), RGB26.3 (BA), RGB26.3A (BA), RGB26.3B (BA)
unnamed: RGB26.6 (GC), RGB26.6A (GC), RGB26.6B (GC), RGB27.1 (GA), RGB27.1A (GA), RGB27.1B (GA)
unnamed: RGB26.5 (RC), RGB26.5A (RC), RGB26.5B (RC), RGB27.2 (RA), RGB27.2A (RA), RGB27.2B (RA)
unnamed: RGB26.4 (BC), RGB26.4A (BC), RGB26.4B (BC), RGB27.3 (BA), RGB27.3A (BA), RGB27.3B (BA)
unnamed: RGB27.6 (GC), RGB27.6A (GC), RGB27.6B (GC), RGB28.1 (GA), RGB28.1A (GA), RGB28.1B (GA)
unnamed: RGB27.5 (RC), RGB27.5A (RC), RGB27.5B (RC), RGB28.2 (RA), RGB28.2A (RA), RGB28.2B (RA)
unnamed: RGB27.4 (BC), RGB27.4A (BC), RGB27.4B (BC), RGB28.3 (BA), RGB28.3A (BA), RGB28.3B (BA)
unnamed: RGB20.1 (GA), RGB20.1A (GA), RGB20.1B (GA), RGB28.6 (GC), RGB28.6A (GC), RGB28.6B (GC)
unnamed: RGB20.2 (RA), RGB20.2A (RA), RGB20.2B (RA), RGB28.5 (RC), RGB28.5A (RC), RGB28.5B (RC)
unnamed: RGB20.3 (BA), RGB20.3A (BA), RGB20.3B (BA), RGB28.4 (BC), RGB28.4A (BC), RGB28.4B (BC)
unnamed: RGB19.1 (GA), RGB19.1A (GA), RGB19.1B (GA), RGB20.6 (GC), RGB20.6A (GC), RGB20.6B (GC)
unnamed: RGB19.2 (RA), RGB19.2A (RA), RGB19.2B (RA), RGB20.5 (RC), RGB20.5A (RC), RGB20.5B (RC)
unnamed: RGB19.3 (BA), RGB19.3A (BA), RGB19.3B (BA), RGB20.4 (BC), RGB20.4A (BC), RGB20.4B (BC)
unnamed: RGB18.1 (GA), RGB18.1A (GA), RGB18.1B (GA), RGB19.6 (GC), RGB19.6A (GC), RGB19.6B (GC)
unnamed: RGB18.2 (RA), RGB18.2A (RA), RGB18.2B (RA), RGB19.5 (RC), RGB19.5A (RC), RGB19.5B (RC)
unnamed: RGB18.3 (BA), RGB18.3A (BA), RGB18.3B (BA), RGB19.4 (BC), RGB19.4A (BC), RGB19.4B (BC)
unnamed: RGB17.1 (GA), RGB17.1A (GA), RGB17.1B (GA), RGB18.6 (GC), RGB18.6A (GC), RGB18.6B (GC)
unnamed: RGB17.2 (RA), RGB17.2A (RA), RGB17.2B (RA), RGB18.5 (RC), RGB18.5A (RC), RGB18.5B (RC)
unnamed: RGB17.3 (BA), RGB17.3A (BA), RGB17.3B (BA), RGB18.4 (BC), RGB18.4A (BC), RGB18.4B (BC)
unnamed: Q7.2 (B1), Q7.4 (B2), U13.1 (OUT)
unnamed: Q7.1 (E1), R24.2
unnamed: Q9.1 (E1), R33.2
unnamed: Q7.3 (E2), R26.2, R28.1, U13.4 (IN-)
unnamed: J5.P$2, R25.1
OTMP: M1.16 (14/A0), U12.5 (OS)
RED_UL: U14.3 (IN+), U15.4 (VO_C)
RULA_1: Q8.5 (C2), Q8.5A (C2), Q8.5A1 (C2), Q8.5B (C2), Q8.5C (C2), Q8.5C1 (C2), Q8.5C2 (C2), Q8.6 (C2), Q8.56 (C2), Q8.56A (C2), Q8.56B (C2), RGB17.5 (RC), RGB17.5A (RC), RGB17.5B (RC)
RULB_1: Q8.7 (C1), Q8.8 (C1), Q8.8A (C1), Q8.8B (C1), Q8.8C (C1), Q8.8C1 (C1), Q8.8C2 (C1), Q8.8C3 (C1), Q8.78 (C1), Q8.78A (C1), Q8.78B (C1), RGB1.5 (RC), RGB1.5A (RC), RGB1.5B (RC)
RX: J6.2, M1.2 (0/RX1/T), U11.3 (A)
RX2: J1.1, J3.1, M1.11 (9/RX2/PWM)
SCLK: M1.15 (13/SCK/LED), U15.7 (SCLK); also elsewhere on the board
SYNC: J5.P$1, R62.1
SYNCIN: M1.21 (19/A5/T/SCL0), R62.2
TX: M1.3 (1/TX1/T), U11.1 (B)
TX2: J1.3, J3.3, M1.12 (10/TX2/PWM)
TXRX: J4.2, U11.4 (X)
UL_EN: M1.20 (18/A4/T/SDA0), U15.6 (!SYNC)
UR_EN: M1.18 (16/A2/T); also elsewhere on the board
V_IR: C34.1, D3.K, R42.2, SH1.1, U17.4 (VIN); also elsewhere on the board
V_RGB: C17.+, C18.+, C27.1, C29.1, C33.1, C37.+, J2.1A, J2.1B, R28.2, R31.2, R40.2, RGB9.1 (GA), RGB9.1A (GA), RGB9.1B (GA), RGB9.2 (RA), RGB9.2A (RA), RGB9.2B (RA), RGB9.3 (BA), RGB9.3A (BA), RGB9.3B (BA), RGB25.1 (GA), RGB25.1A (GA), RGB25.1B (GA), RGB25.2 (RA), RGB25.2A (RA), RGB25.2B (RA), RGB25.3 (BA), RGB25.3A (BA), RGB25.3B (BA), SH1.2; also elsewhere on the board

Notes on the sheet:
TODO: - R17 as 1206 (inductor?) - fixed SS on J6
LED and SYNC
MODULAR
DAISY- CHAIN
OVERTEMP MONITOR
